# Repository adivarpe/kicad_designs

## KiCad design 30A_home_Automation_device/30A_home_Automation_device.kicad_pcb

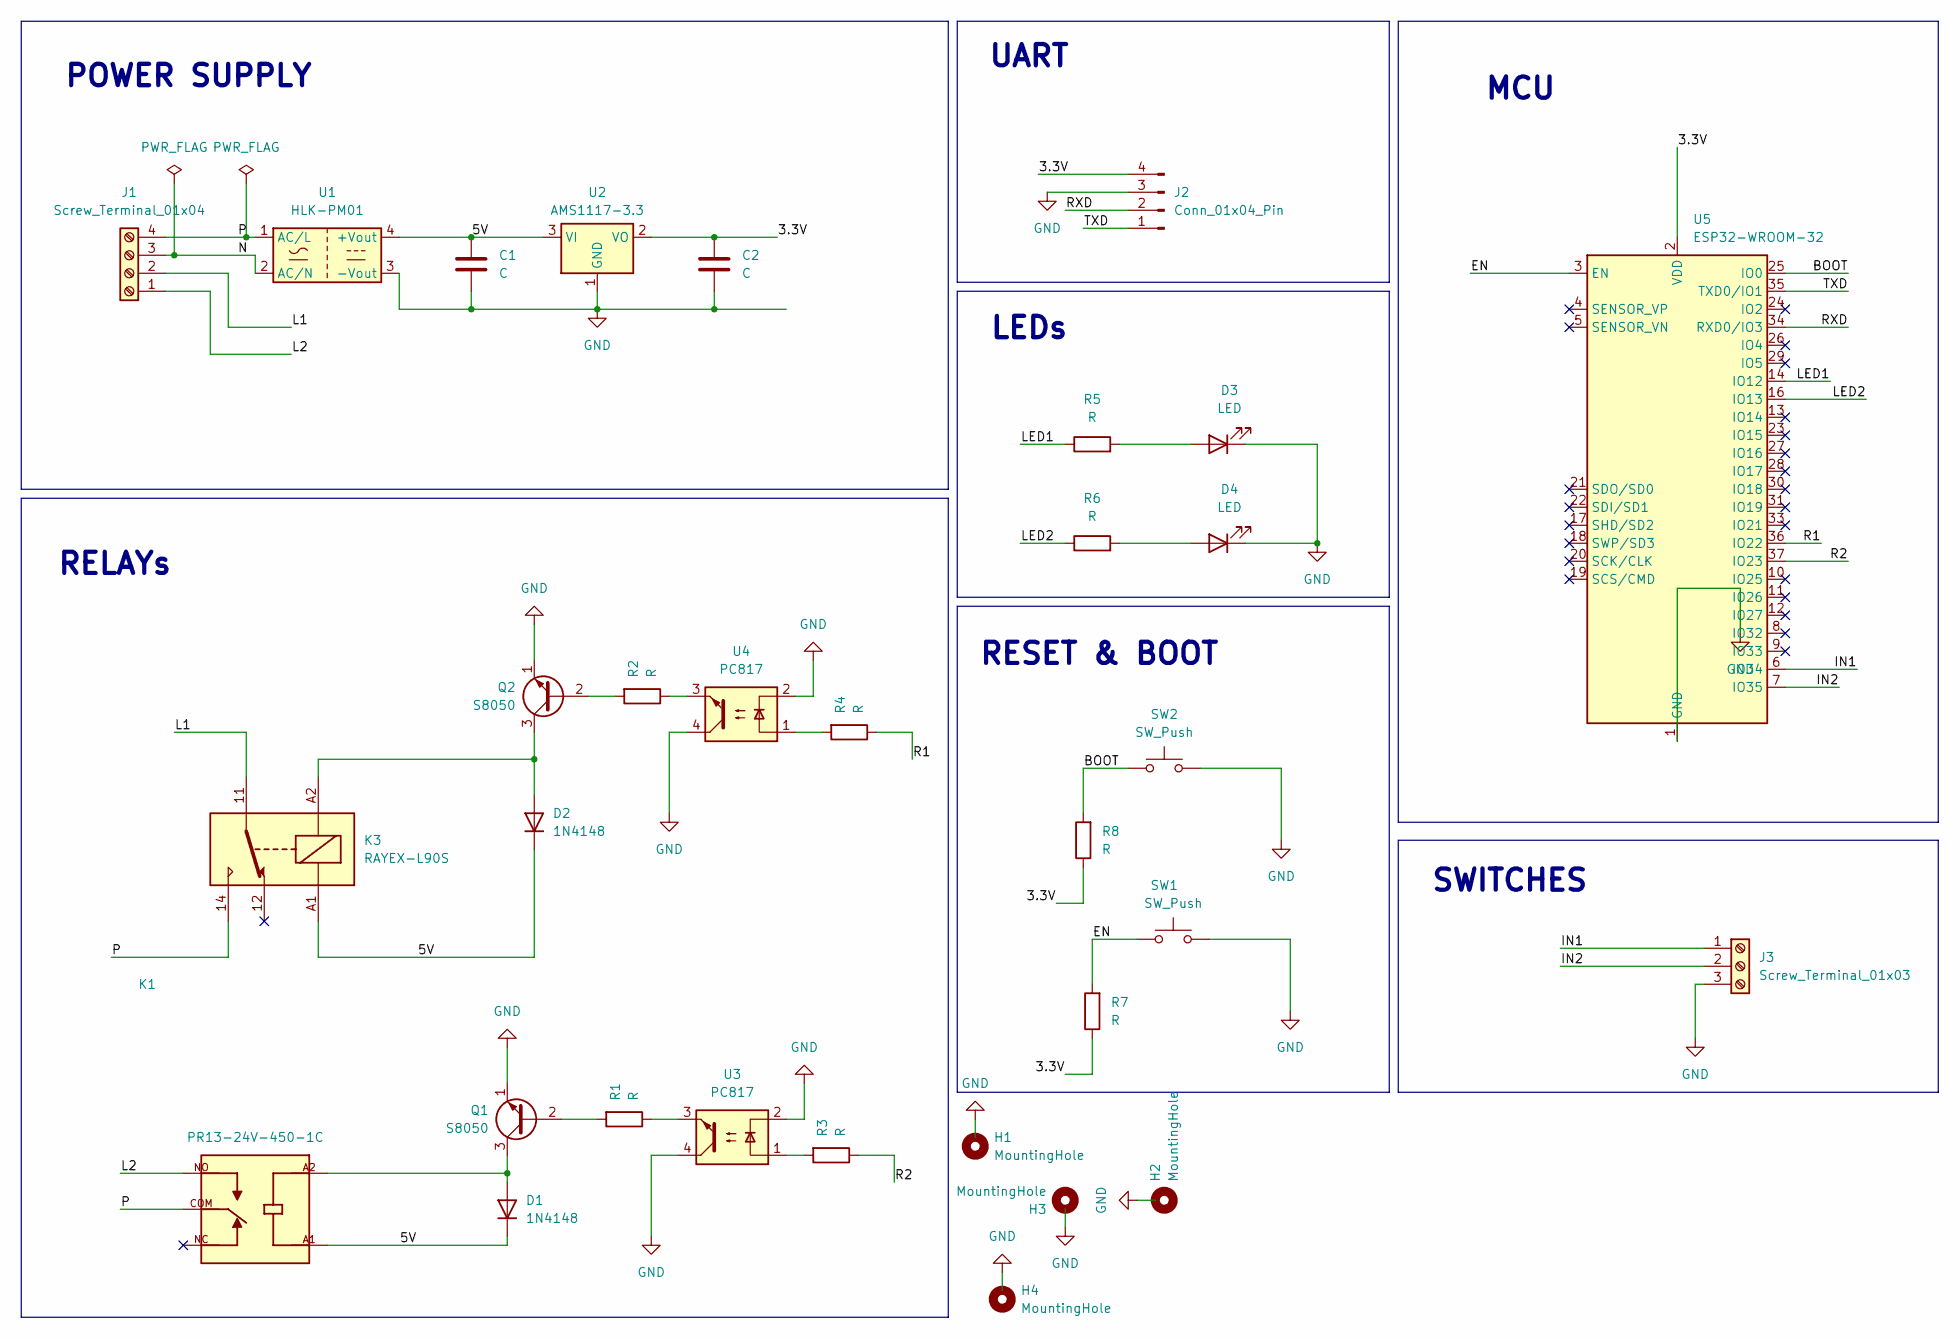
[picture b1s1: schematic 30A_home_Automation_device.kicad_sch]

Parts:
C1, C2: C; C_0805_2012Metric
D1, D2: 1N4148; D_DO-35_SOD27_P7.62mm_Horizontal
D3, D4: LED; LED_0805_2012Metric
H1, H2, H3, H4: MountingHole; MountingHole_2.7mm_M2.5_ISO7380_Pad_TopBottom
J1: Screw_Terminal_01x04; TerminalBlock_MaiXu_MX126-5.0-04P_1x04_P5.00mm
J2: Conn_01x04_Pin; PinHeader_1x04_P2.54mm_Vertical
J3: Screw_Terminal_01x03; TerminalBlock_MaiXu_MX126-5.0-03P_1x03_P5.00mm
K1: PR13-24V-450-1C; RELAY_PR13-24V-450-1C; PARTREV 1.0
K3: RAYEX-L90S; Relay_SPDT_RAYEX-L90S
Q1, Q2: S8050; TO-92_Inline
R1, R2, R3, R4, R5, R6, R7, R8: R; R_0805_2012Metric
SW1, SW2: SW_Push; SW_TH_Tactile_Omron_B3F-102x
U1: HLK-PM01; Converter_ACDC_Hi-Link_HLK-PMxx
U2: AMS1117-3.3; SOT-223-3_TabPin2
U3, U4: PC817; DIP-4_W7.62mm
U5: ESP32-WROOM-32

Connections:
/3.3V: C2.1, J2.4, R7.1, R8.1, U2.2 (VO), U5.2 (VDD)
/5V: C1.1, D1.1 (K), D2.1 (K), K1.A1, K3.A1, U1.4 (+Vout), U2.3 (VI)
/BOOT: R8.2, SW2.1, U5.25 (IO0)
/EN: R7.2, SW1.1, U5.3 (EN)
/IN1: J3.1, U5.6 (IO34)
/IN2: J3.2, U5.7 (IO35)
/L1: J1.2, K3.11
/L2: J1.1, K1.NO
/LED1: R5.1, U5.14 (IO12)
/LED2: R6.1, U5.16 (IO13)
/N: J1.3, U1.2 (AC/N)
/P: J1.4, K1.COM, K3.14, U1.1 (AC/L)
/R1: R4.1, U5.36 (IO22)
/R2: R3.1, U5.37 (IO23)
/RXD: J2.2, U5.34 (RXD0/IO3)
/TXD: J2.1, U5.35 (TXD0/IO1)
GND: C1.2, C2.2, D3.1 (K), D4.1 (K), J2.3, J3.3, Q1.1 (E), Q2.1 (E), SW1.2, SW2.2, U1.3 (-Vout), U2.1 (GND), U3.2, U3.4, U4.2, U4.4, U5.1 (GND), U5.15 (GND), U5.38 (GND), U5.39 (GND)
unnamed: D1.2 (A), K1.A2, Q1.3 (C)
unnamed: D2.2 (A), K3.A2, Q2.3 (C)
unnamed: D3.2 (A), R5.2
unnamed: D4.2 (A), R6.2
unnamed: Q1.2 (B), R1.2
unnamed: Q2.2 (B), R2.2
unnamed: R1.1, U3.3
unnamed: R2.1, U4.3
unnamed: R3.2, U3.1
unnamed: R4.2, U4.1

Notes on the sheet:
MCU
RESET & BOOT
POWER SUPPLY
RELAYs
SWITCHES
UART
LEDs

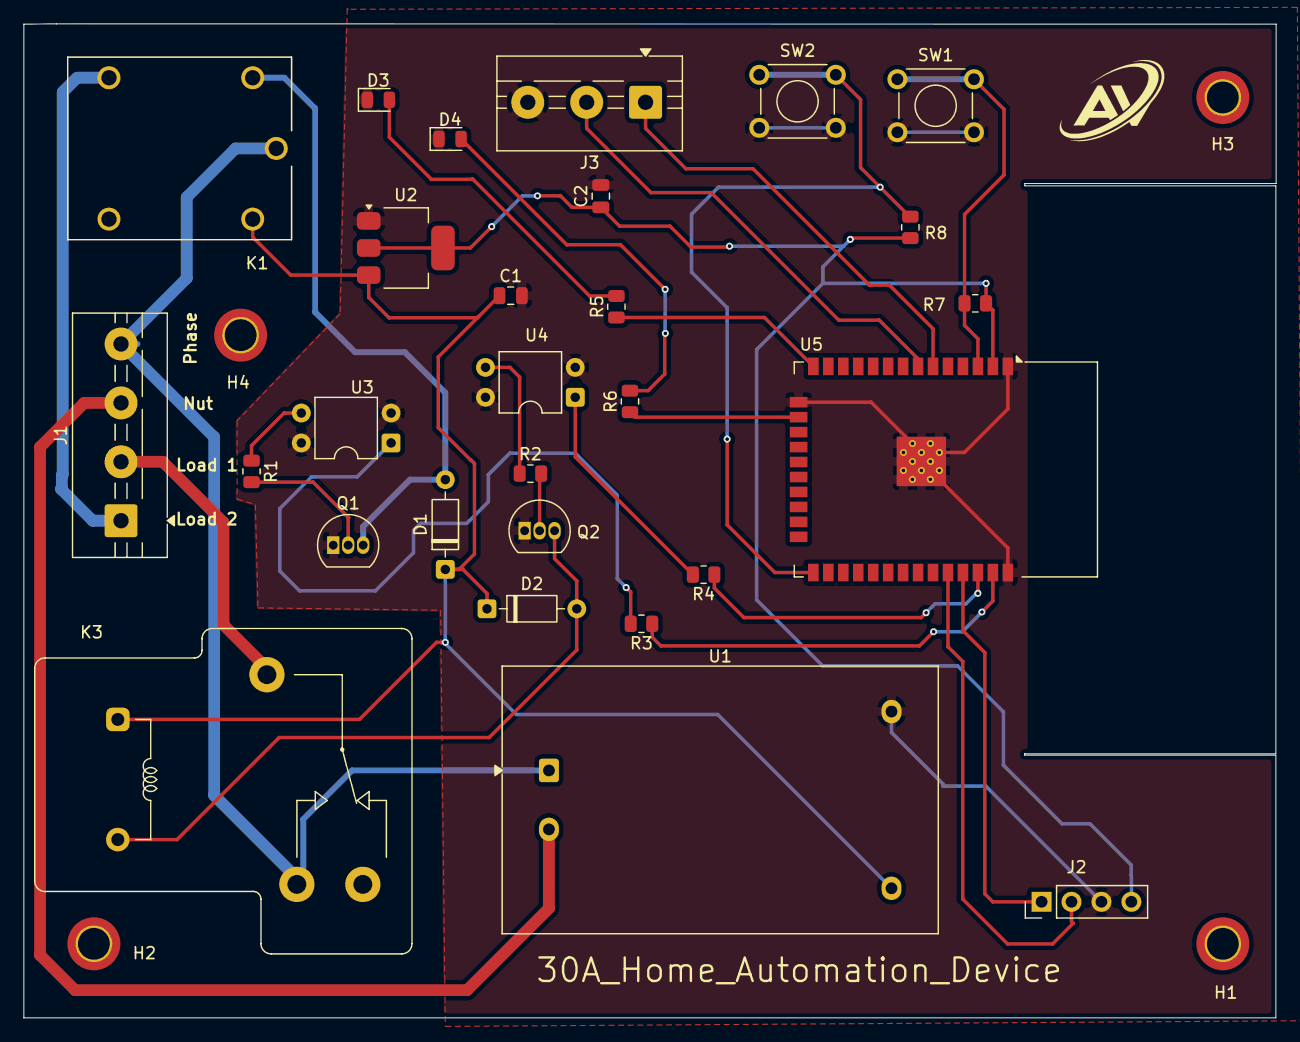
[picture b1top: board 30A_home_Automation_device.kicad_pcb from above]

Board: 2 copper layers, 106.3 x 84.4 mm, 32 parts (0 on the bottom side), 27 nets.

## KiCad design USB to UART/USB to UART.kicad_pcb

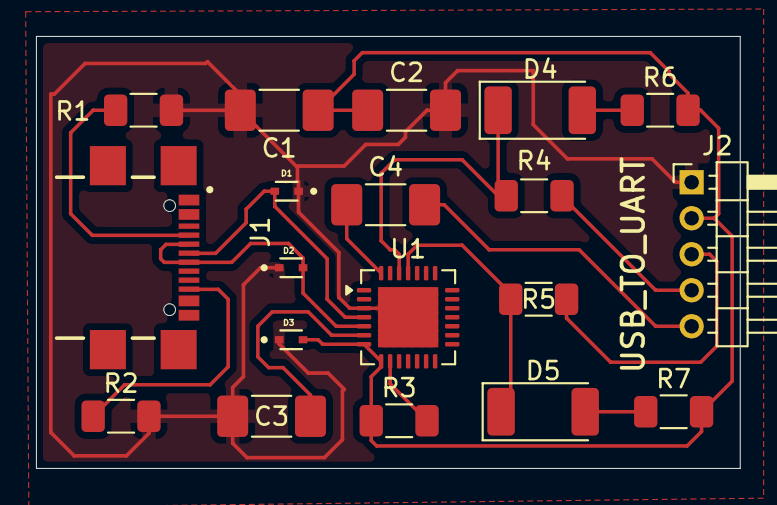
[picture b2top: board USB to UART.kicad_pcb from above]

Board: 2 copper layers, 39.1 x 24.0 mm, 19 parts (0 on the bottom side), 16 nets.

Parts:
C1, C2, C3, C4: 100nf; C_1808_4520Metric_Pad1.72x2.30mm_HandSolder
D1, D2, D3: LESD5D5.0CT1G; TVS_LESD5D5.0CT1G
D4, D5: LED; LED_2010_5025Metric_Pad1.52x2.65mm_HandSolder
J1: USB_C_Receptacle_USB2.0_16P; GCT_USB4940-00-A_REVA
J2: Conn_01x05_Pin; PinHeader_1x05_P2.00mm_Horizontal
R1, R2: 5.1k; R_1206_3216Metric_Pad1.30x1.75mm_HandSolder
R3: 10k; R_1206_3216Metric_Pad1.30x1.75mm_HandSolder
R4, R5, R6, R7: 1k; R_1206_3216Metric_Pad1.30x1.75mm_HandSolder
U1: CP2102N-Axx-xQFN28; QFN-28-1EP_5x5mm_P0.5mm_EP3.35x3.35mm

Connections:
/+D: D1.2, J1.A6 (D+), J1.B6 (D+), U1.4 (D+)
/-D: D2.2, J1.A7 (D-), J1.B7 (D-), U1.5 (D-)
/RST: C4.2, J2.5
/RX: J2.3, R5.2
/TX: J2.4, R4.2
/vbus: C1.1, C2.1, D3.2, J2.2, R3.1, R6.2, R7.2, U1.7 (VREGIN), U1.8 (VBUS)
GND: C1.2, C2.2, C3.1, D1.1, D2.1, D3.1, J2.1, R1.2, R2.2, U1.3 (GND), U1.29 (GND)
unnamed: D4.2 (A), R6.1
unnamed: D4.1 (K), R4.1, U1.26 (TXD)
unnamed: D5.2 (A), R7.1
unnamed: D5.1 (K), R5.1, U1.25 (RXD)
unnamed: J1.A5 (CC1), R1.1
unnamed: J1.B5 (CC2), R2.1
unnamed: C3.2, U1.6 (VDD)
unnamed: C4.1, U1.28 (~DTR)
unnamed: R3.2, U1.9 (~RST)

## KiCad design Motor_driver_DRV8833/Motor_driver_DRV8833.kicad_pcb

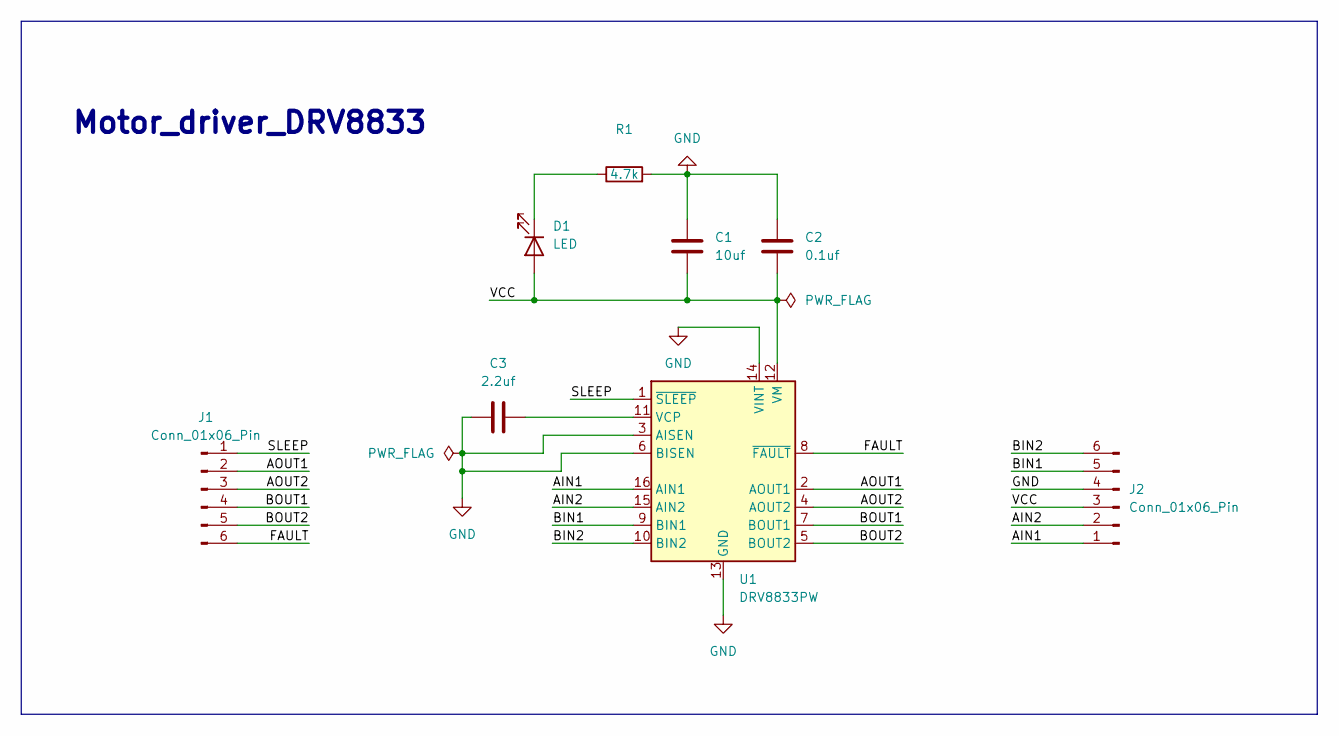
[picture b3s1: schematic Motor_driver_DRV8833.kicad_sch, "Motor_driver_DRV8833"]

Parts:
C1: 10uf; C_1812_4532Metric
C2: 0.1uf; C_1812_4532Metric
C3: 2.2uf; C_1812_4532Metric
D1: LED; LED_1210_3225Metric
J1, J2: Conn_01x06_Pin; PinHeader_1x06_P2.54mm_Vertical
R1: 4.7k; R_0603_1608Metric
U1: DRV8833PW; TSSOP-16_4.4x5mm_P0.65mm

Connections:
/AIN1: J2.1, U1.16 (AIN1)
/AIN2: J2.2, U1.15 (AIN2)
/AOUT1: J1.2, U1.2 (AOUT1)
/AOUT2: J1.3, U1.4 (AOUT2)
/BIN1: J2.5, U1.9 (BIN1)
/BIN2: J2.6, U1.10 (BIN2)
/BOUT1: J1.4, U1.7 (BOUT1)
/BOUT2: J1.5, U1.5 (BOUT2)
/FAULT: J1.6, U1.8 (~FAULT)
/SLEEP: J1.1, U1.1 (~SLEEP)
/VCC: C1.2, C2.2, D1.2 (A), J2.3, U1.12 (VM)
GND: C1.1, C2.1, C3.1, J2.4, R1.2, U1.3 (AISEN), U1.6 (BISEN), U1.13 (GND), U1.14 (VINT)
unnamed: D1.1 (K), R1.1
unnamed: C3.2, U1.11 (VCP)

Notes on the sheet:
Motor_driver_DRV8833

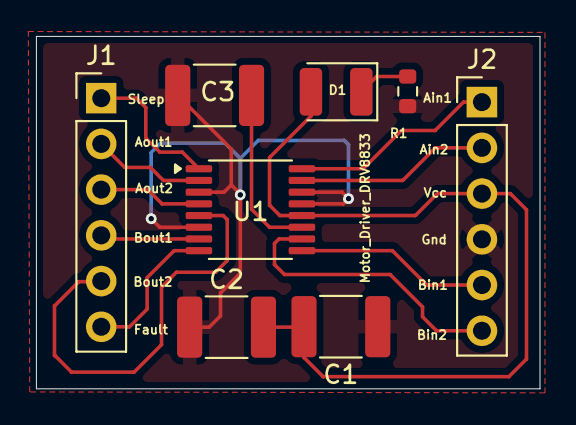
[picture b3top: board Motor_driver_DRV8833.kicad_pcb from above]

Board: 2 copper layers, 28.0 x 19.6 mm, 8 parts (0 on the bottom side), 14 nets.

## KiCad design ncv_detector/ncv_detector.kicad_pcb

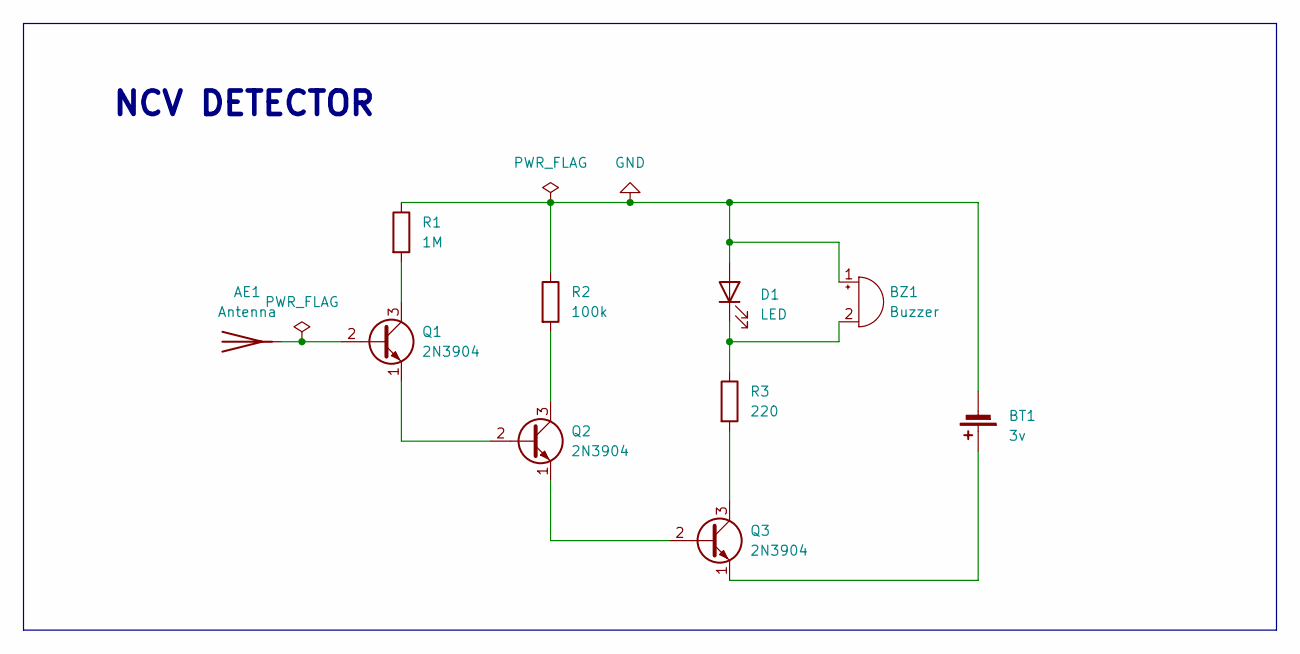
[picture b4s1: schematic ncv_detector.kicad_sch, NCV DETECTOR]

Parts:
AE1: Antenna; PinHeader_1x01_P2.54mm_Horizontal
BT1: 3v; BatteryHolder_Bulgin_BX0034_1xAAA
BZ1: Buzzer; Buzzer_15x7.5RM7.6
D1: LED; LED_D5.0mm
Q1, Q2, Q3: 2N3904; TO-92_Inline
R1: 1M; R_Axial_DIN0204_L3.6mm_D1.6mm_P7.62mm_Horizontal
R2: 100k; R_Axial_DIN0204_L3.6mm_D1.6mm_P7.62mm_Horizontal
R3: 220; R_Axial_DIN0204_L3.6mm_D1.6mm_P7.62mm_Horizontal

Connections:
GND: BT1.2 (-), BZ1.1 (+), D1.2 (A), R1.1, R2.1
unnamed: AE1.1 (A_1), Q1.2 (B)
unnamed: BT1.1 (+), Q3.1 (E)
unnamed: BZ1.2 (-), D1.1 (K), R3.1
unnamed: Q1.3 (C), R1.2
unnamed: Q1.1 (E), Q2.2 (B)
unnamed: Q2.3 (C), R2.2
unnamed: Q2.1 (E), Q3.2 (B)
unnamed: Q3.3 (C), R3.2

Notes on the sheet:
NCV DETECTOR

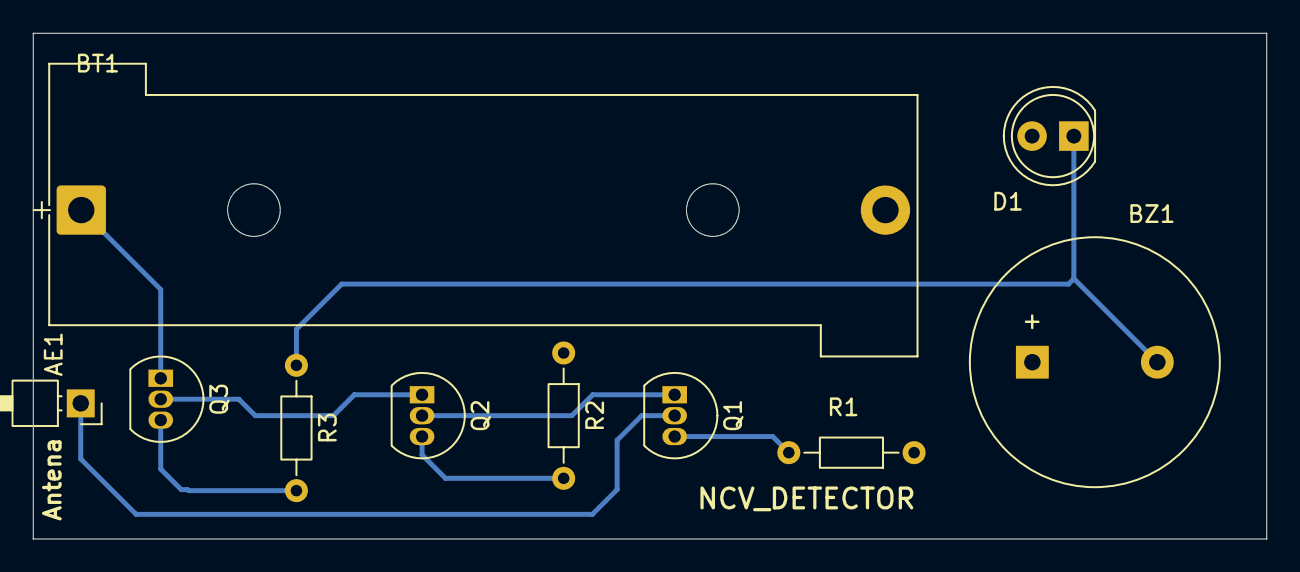
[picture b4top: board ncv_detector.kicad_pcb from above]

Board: 2 copper layers, 75.0 x 30.8 mm, 10 parts (0 on the bottom side), 9 nets.

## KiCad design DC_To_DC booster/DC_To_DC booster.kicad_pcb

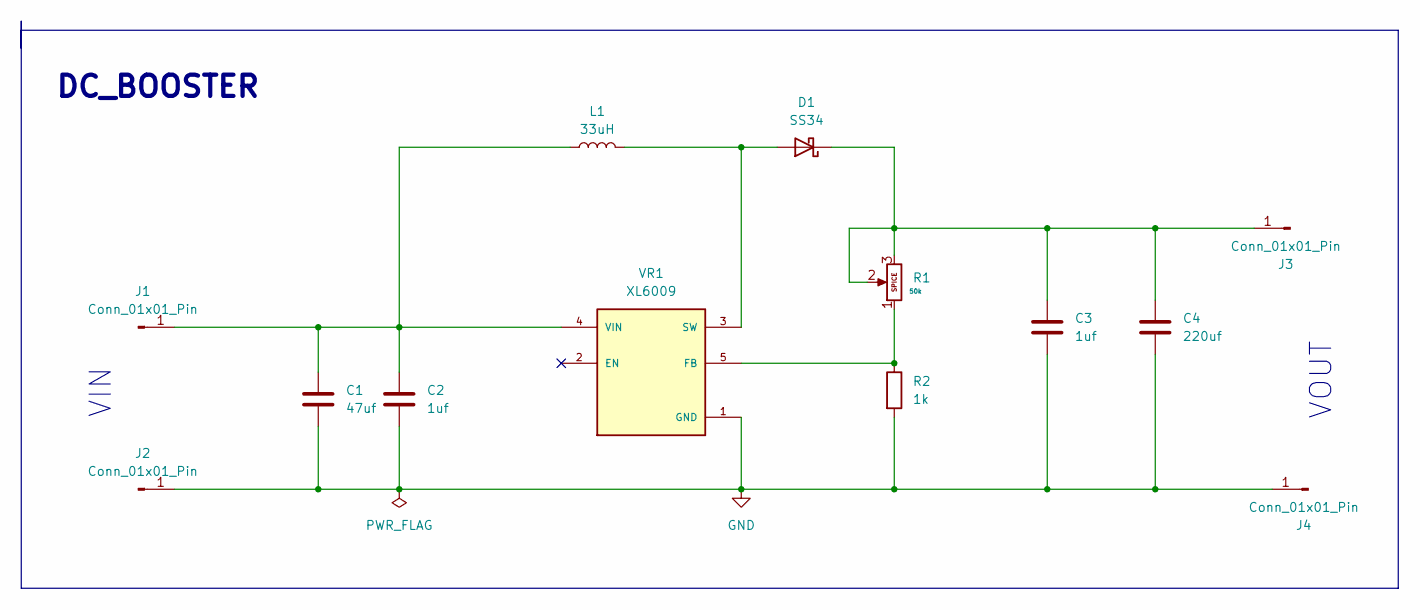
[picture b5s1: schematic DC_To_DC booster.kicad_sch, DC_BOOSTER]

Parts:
C1: 47uf; CP_Radial_D5.0mm_P2.50mm
C2, C3: 1uf; C_1206_3216Metric
C4: 220uf; CP_Radial_D5.0mm_P2.50mm
D1: SS34; D_SMA
J1, J2, J3, J4: Conn_01x01_Pin; PinHeader_1x01_P2.00mm_Horizontal
L1: 33uH; L_12x12mm_H8mm
R1: Potentiometer; Potentiometer_Bourns_3296W_Vertical
R2: 1k; R_0805_2012Metric
VR1: XL6009; DPAK170P1435X465-6N; PARTREV 1.1

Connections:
GND: C1.2, C2.2, C3.2, C4.2, J2.1 (Pin_1_1), J4.1 (Pin_1_1), R2.2, VR1.1 (GND)
unnamed: D1.2 (A), L1.2, VR1.3 (SW), VR1.6 (SW)
unnamed: C3.1, C4.1, D1.1 (K), J3.1 (Pin_1_1), R1.2, R1.3
unnamed: C1.1, C2.1, J1.1 (Pin_1_1), L1.1, VR1.4 (VIN)
unnamed: R1.1, R2.1, VR1.5 (FB)

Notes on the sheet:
VIN
VOUT
DC_BOOSTER

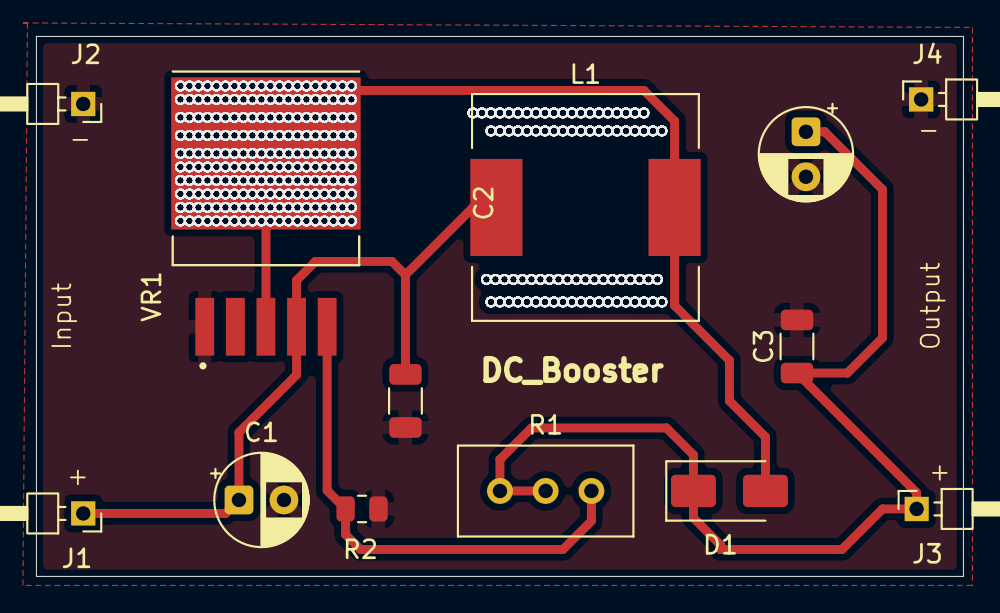
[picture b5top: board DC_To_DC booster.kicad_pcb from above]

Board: 2 copper layers, 51.5 x 30.0 mm, 13 parts (0 on the bottom side), 5 nets.

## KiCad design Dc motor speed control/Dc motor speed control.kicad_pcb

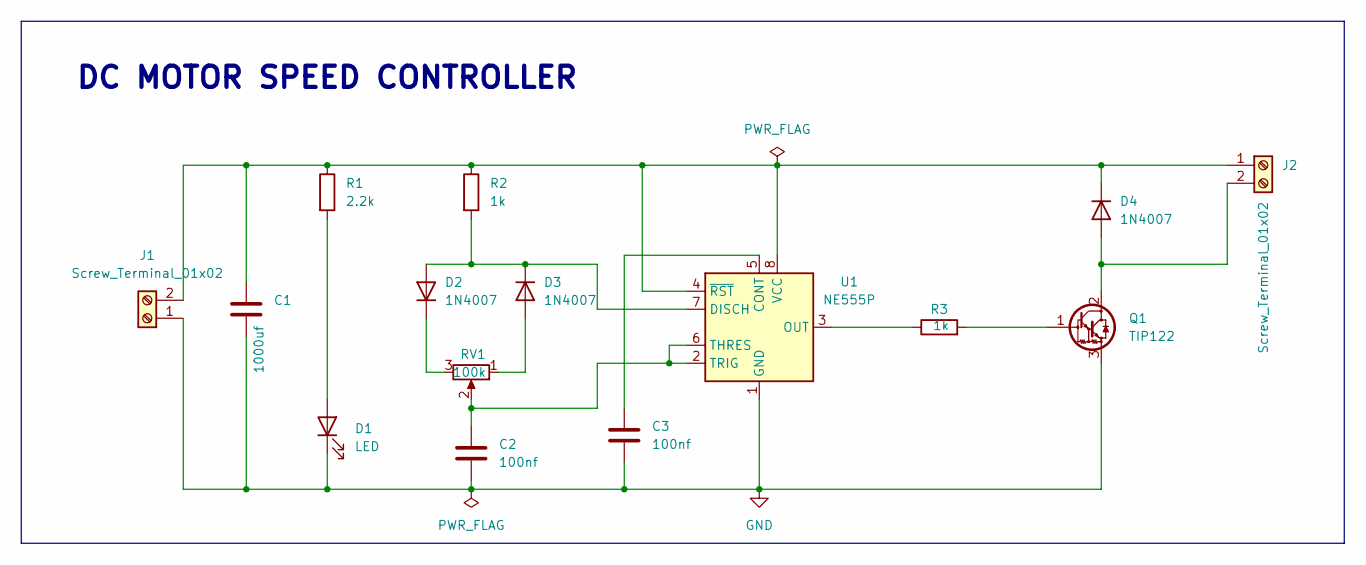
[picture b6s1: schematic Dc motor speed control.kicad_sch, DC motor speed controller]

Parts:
C1: 1000uf; C_Disc_D4.7mm_W2.5mm_P5.00mm
C2: 100nf; C_Disc_D4.7mm_W2.5mm_P5.00mm
C3: 100nf; CP_Radial_D7.5mm_P2.50mm
D1: LED; LED_D5.0mm
D2, D3, D4: 1N4007; D_DO-41_SOD81_P10.16mm_Horizontal
J1, J2: Screw_Terminal_01x02; TerminalBlock_4Ucon_1x02_P3.50mm_Horizontal
Q1: TIP122; TO-220-3_Vertical
R1: 2.2k; R_Axial_DIN0207_L6.3mm_D2.5mm_P10.16mm_Horizontal
R2, R3: 1k; R_Axial_DIN0207_L6.3mm_D2.5mm_P10.16mm_Horizontal
RV1: 100k; Potentiometer_Alps_RK163_Single_Horizontal
U1: NE555P; DIP-8_W7.62mm

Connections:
GND: C1.2, C2.2, C3.2, D1.1 (K), J1.1, Q1.3 (E), U1.1 (GND)
unnamed: D1.2 (A), R1.2
unnamed: D2.2 (A), D3.1 (K), R2.2, U1.7 (DISCH)
unnamed: D2.1 (K), RV1.3
unnamed: D3.2 (A), RV1.1
unnamed: D4.2 (A), J2.2, Q1.2 (C)
unnamed: C1.1, D4.1 (K), J1.2, J2.1, R1.1, R2.1, U1.4 (~RST), U1.8 (VCC)
unnamed: Q1.1 (B), R3.2
unnamed: C3.1, U1.5 (CONT)
unnamed: R3.1, U1.3 (OUT)
unnamed: C2.1, RV1.2, U1.2 (TRIG), U1.6 (THRES)

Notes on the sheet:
DC MOTOR SPEED CONTROLLER

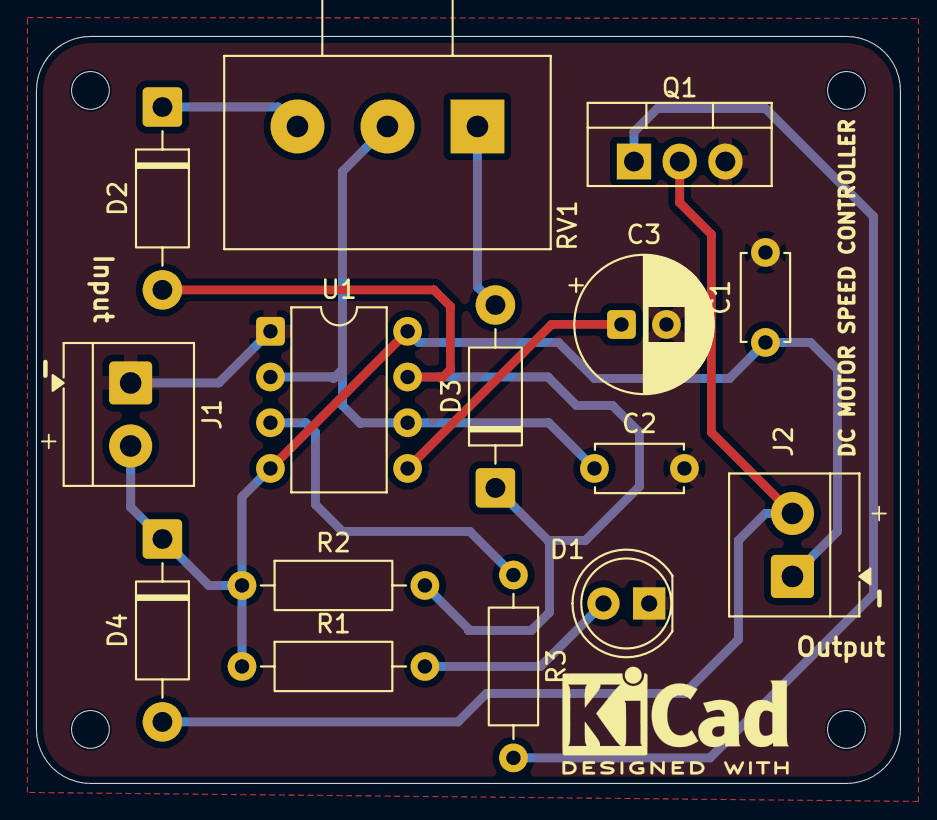
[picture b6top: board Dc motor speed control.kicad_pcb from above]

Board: 2 copper layers, 48.0 x 41.5 mm, 15 parts (0 on the bottom side), 11 nets.

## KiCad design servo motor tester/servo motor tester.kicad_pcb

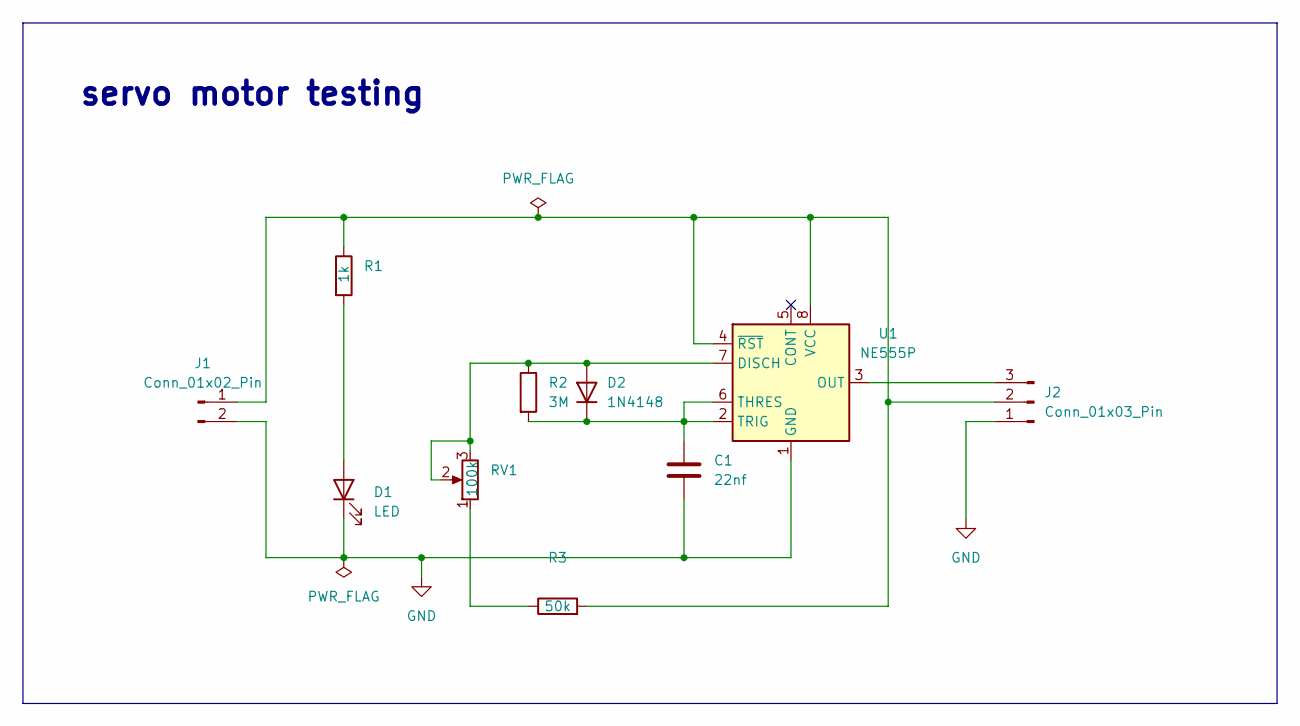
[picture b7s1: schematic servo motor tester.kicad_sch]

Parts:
C1: 22nf; C_Disc_D3.8mm_W2.6mm_P2.50mm
D1: LED; LED_D3.0mm
D2: 1N4148; D_DO-35_SOD27_P7.62mm_Horizontal
J1: Conn_01x02_Pin; PinHeader_1x02_P2.54mm_Horizontal
J2: Conn_01x03_Pin; PinHeader_1x03_P2.54mm_Horizontal
R1: 1k; R_Axial_DIN0207_L6.3mm_D2.5mm_P10.16mm_Horizontal
R2: 3M; R_Axial_DIN0207_L6.3mm_D2.5mm_P10.16mm_Horizontal
R3: 50k; R_Axial_DIN0207_L6.3mm_D2.5mm_P10.16mm_Horizontal
RV1: 100k; Potentiometer_Alps_RK163_Single_Horizontal
U1: NE555P; DIP-8_W7.62mm

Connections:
GND: C1.2, D1.1 (K), J1.2, J2.1, U1.1 (GND)
unnamed: D1.2 (A), R1.2
unnamed: D2.2 (A), R2.1, RV1.2, RV1.3, U1.7 (DISCH)
unnamed: C1.1, D2.1 (K), R2.2, U1.2 (TRIG), U1.6 (THRES)
unnamed: J1.1, J2.2, R1.1, R3.2, U1.4 (~RST), U1.8 (VCC)
unnamed: J2.3, U1.3 (OUT)
unnamed: R3.1, RV1.1

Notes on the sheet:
servo motor testing

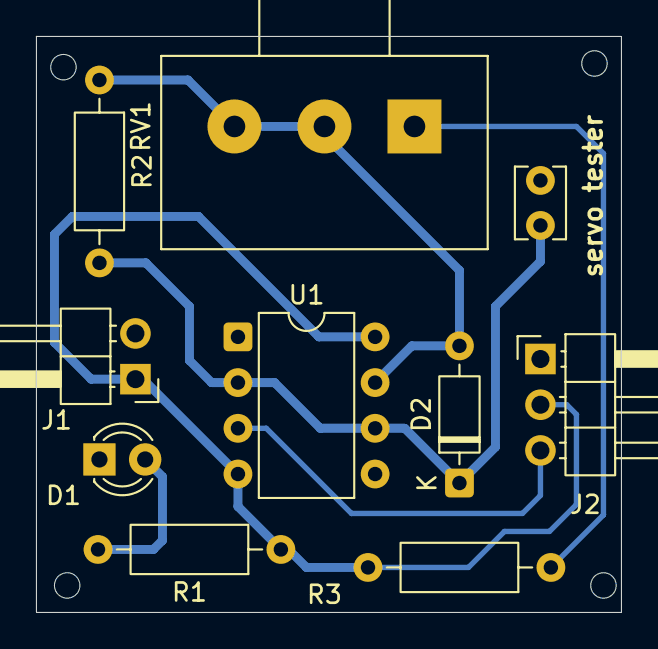
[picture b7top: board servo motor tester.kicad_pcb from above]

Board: 2 copper layers, 32.5 x 32.0 mm, 10 parts (0 on the bottom side), 7 nets.

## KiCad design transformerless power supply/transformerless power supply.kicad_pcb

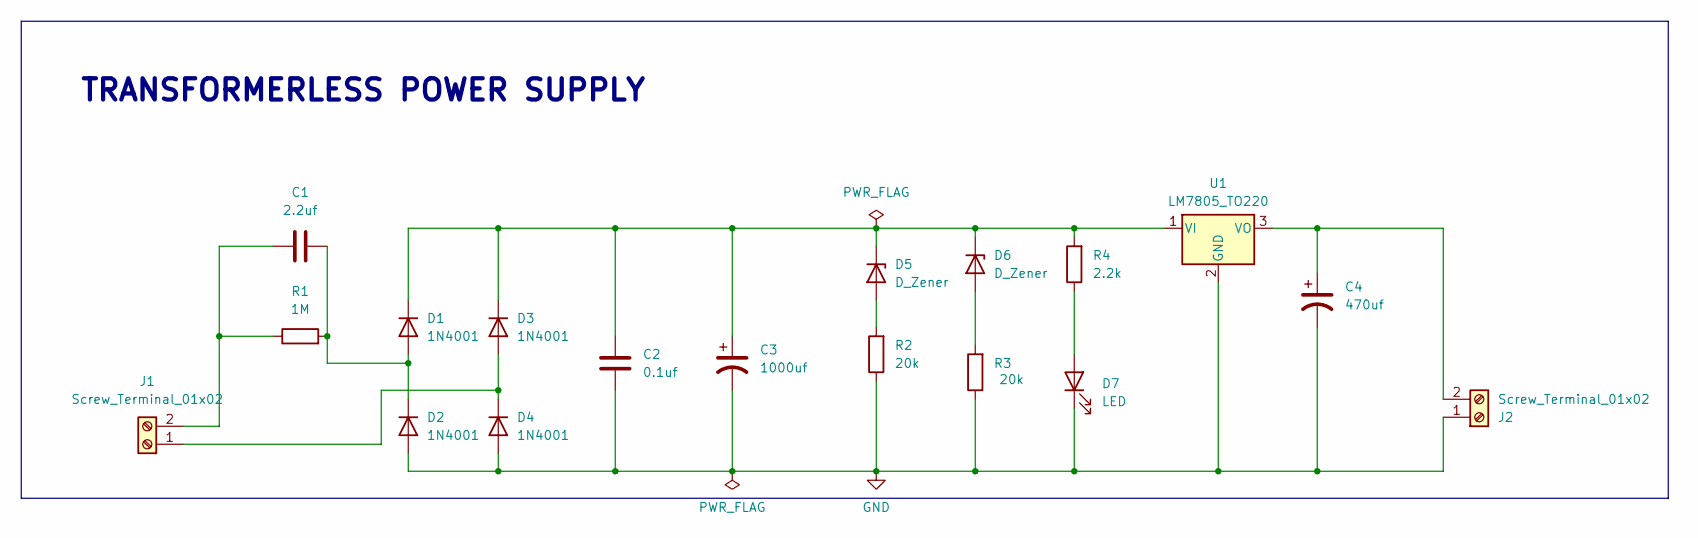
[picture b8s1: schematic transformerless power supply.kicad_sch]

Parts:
C1: 2.2uf; CP_Radial_D7.5mm_P2.50mm
C2: 0.1uf; CP_Radial_D7.5mm_P2.50mm
C3: 1000uf; CP_Radial_D8.0mm_P3.80mm
C4: 470uf; CP_Radial_D8.0mm_P3.80mm
D1, D2, D3, D4: 1N4001; D_DO-41_SOD81_P10.16mm_Horizontal
D5, D6: D_Zener; D_DO-41_SOD81_P10.16mm_Horizontal
D7: LED; LED_D3.0mm
J1, J2: Screw_Terminal_01x02; TerminalBlock_MaiXu_MX126-5.0-02P_1x02_P5.00mm
R1: 1M; R_Axial_DIN0207_L6.3mm_D2.5mm_P10.16mm_Horizontal
R2, R3: 20k; R_Axial_DIN0207_L6.3mm_D2.5mm_P10.16mm_Horizontal
R4: 2.2k; R_Axial_DIN0207_L6.3mm_D2.5mm_P10.16mm_Horizontal
U1: LM7805_TO220; TO-220-3_Vertical

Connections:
unnamed: C1.2, D1.2 (A), D2.1 (K), R1.2
unnamed: C2.2, C3.1, D1.1 (K), D3.1 (K), D5.1 (K), D6.1 (K), R4.2, U1.1 (VI)
unnamed: C2.1, C3.2, C4.2, D2.2 (A), D4.2 (A), D7.1 (K), J2.1, R2.1, R3.1, U1.2 (GND)
unnamed: D3.2 (A), D4.1 (K), J1.1
unnamed: D5.2 (A), R2.2
unnamed: D6.2 (A), R3.2
unnamed: D7.2 (A), R4.1
unnamed: C1.1, J1.2, R1.1
unnamed: C4.1, J2.2, U1.3 (VO)

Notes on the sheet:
TRANSFORMERLESS POWER SUPPLY

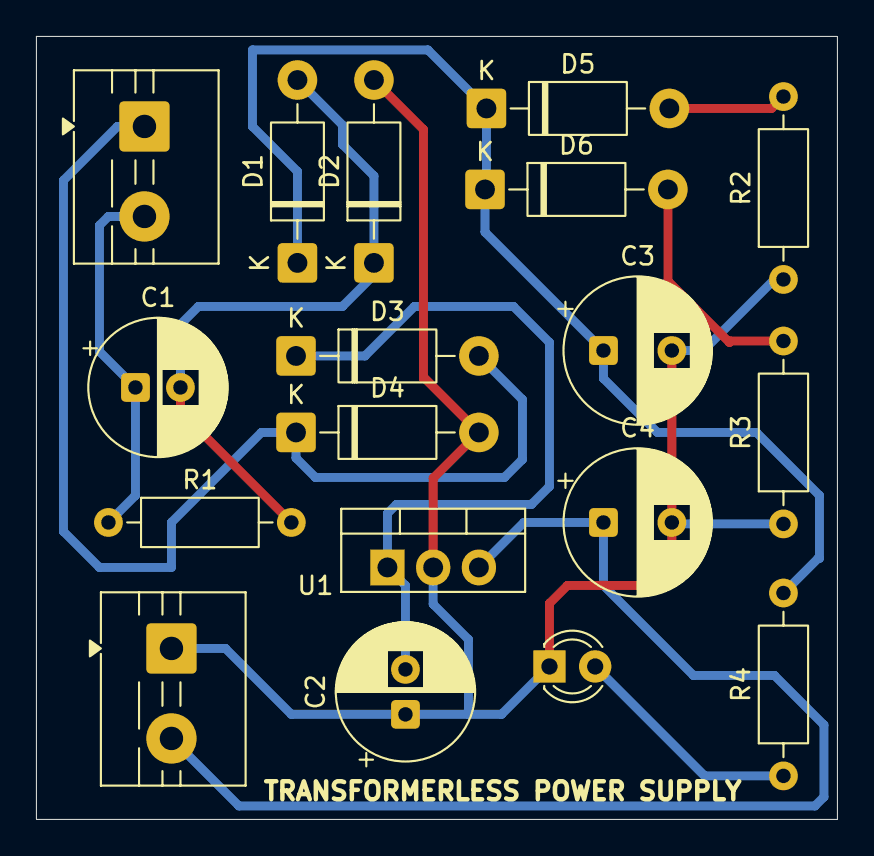
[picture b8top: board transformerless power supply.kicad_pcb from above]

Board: 2 copper layers, 44.5 x 43.5 mm, 18 parts (0 on the bottom side), 9 nets.
